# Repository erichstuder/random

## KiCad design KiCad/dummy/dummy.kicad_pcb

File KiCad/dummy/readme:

pcb with traces of different width

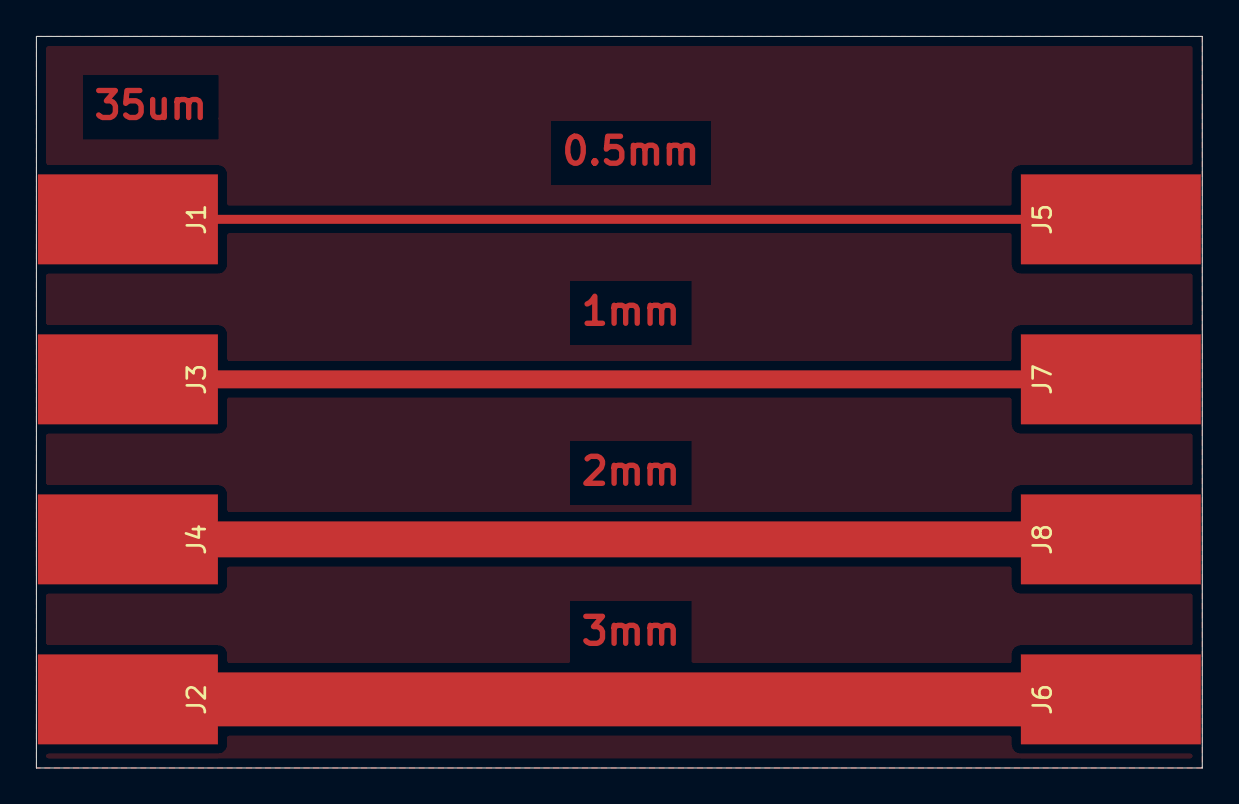
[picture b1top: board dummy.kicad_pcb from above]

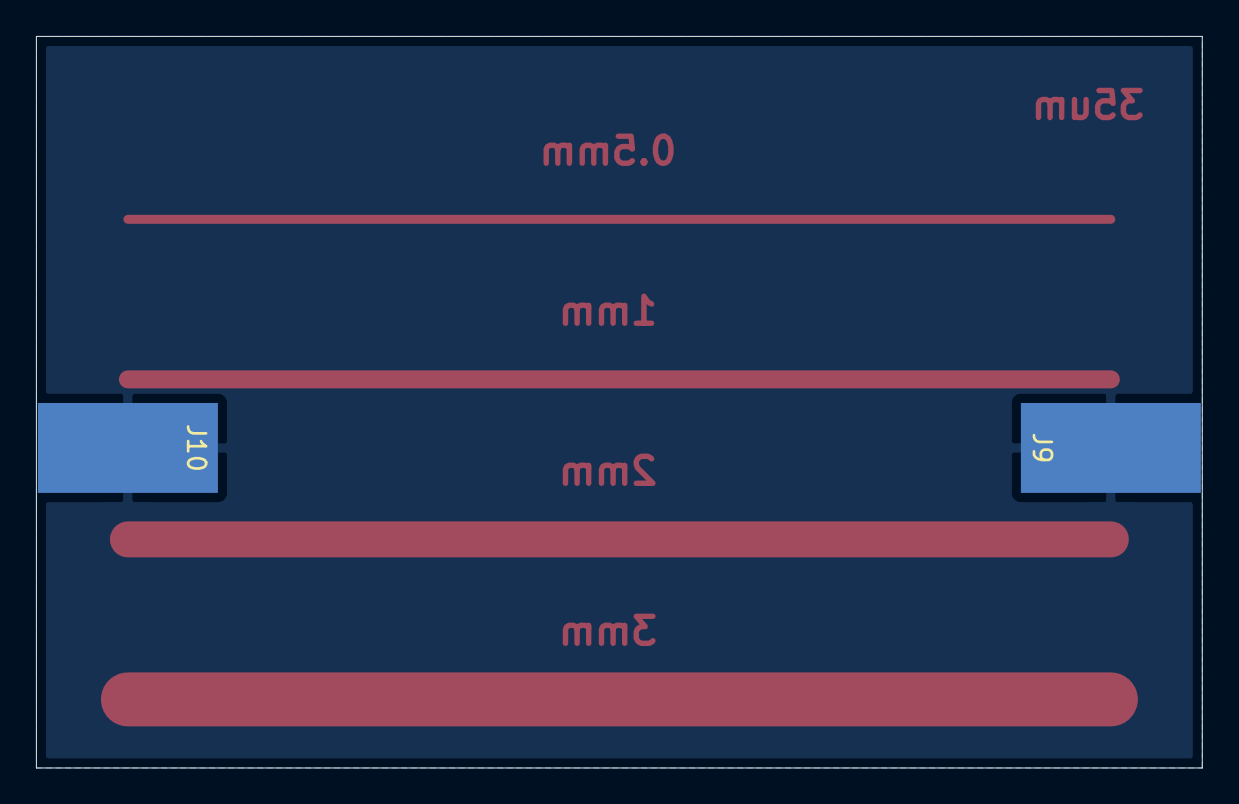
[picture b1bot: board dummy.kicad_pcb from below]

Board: 2 copper layers, 64.8 x 40.6 mm, 10 parts (2 on the bottom side), 5 nets.

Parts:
J1, J2, J3, J4, J5, J6, J7, J8, J9, J10: Conn_01x01_Female; SolderWirePad_1x01_SMD_5x10mm

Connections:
unnamed: J1.1, J5.1
unnamed: J2.1, J6.1
unnamed: J3.1, J7.1
unnamed: J4.1, J8.1
unnamed: J9.1, J10.1

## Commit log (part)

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2019-08-17 added new folder
2019-08-18 made it work for windows and some cleanup
2019-08-18 images for training created
2019-08-20 deleted old file
2019-08-29 added some rules for HDL languages
2019-09-03 example with parameters
2019-09-04 idea for an uart. But not yet compiling
2019-09-05 finally compiling
2019-09-05 resolved some more warnings
2019-09-07 initial commit of clock definition
2019-09-07 random commit
    test benches added
2019-09-07 simplified and tested UartTx
2019-09-07 added some stuff to ignore
2019-09-08 some try around with debugging possibilities
2019-09-09 added file to project
2019-09-10 top level design of I2C Master started
2019-09-11 some hacking with tasks (not compiling)
2019-09-11 random commit
2019-09-22 looks fine till now
    next step is to read from slave
2019-09-22 started cleaner setup of code
2019-09-25 made more files to increase readability
2019-09-26 some new files and more tryout
2019-09-28 ignoring *.bak files
2019-09-28 proof of conecept: abstraction with packages
2019-09-28 refactored to package usage
2019-09-28 added and integrated ReadBit as a package
2019-09-28 further work
2019-09-28 integrated readByte
2019-09-28 integrated SendStop
2019-09-29 some file reordering
2019-09-29 added some simple testing idea (not yet perfect)
2019-09-29 added another chapter
2019-09-30 started with error handling chapter
2019-10-01 finished chapter
2019-10-01 started next chapter
2019-10-02 added chapter about unit tests
2019-10-03 added Classes chapter
2019-10-05 test project for TCS34725 with arduino leonardo
2019-10-12 added Systems chapter
2019-10-12 added chapter about Concurrency
2019-10-14 added G15
2019-10-14 added some more lines
2019-10-26 inital commit
2019-10-27 first version of iot luxmeter
2019-10-27 a playaround project for Google Test
2020-04-05 creation of simple terminal for leonardo
2020-04-05 added unit tests
2020-04-10 bugfixes and minor modifications
2020-04-10 simple script for water detection
2020-04-25 added more leds for better visibility
2020-04-25 updated unit tests
2020-05-23 some code snippets
2020-05-23 another snippet
2020-06-14 didn't work
2020-06-20 initial creation
2020-06-27 rework and cleanup
2020-06-27 refactored for more clarity
2020-07-12 update modified submodule
2020-07-15 added locks
2020-07-18 ready to print
2020-07-18 sliced and files moved to folder
2020-07-18 some cleanup
2020-07-18 modified due to printing problems
2020-07-18 tryout of other print parameters
2020-07-19 simplified the model
2020-07-19 Moved from its own repository to here.
2020-07-20 added a grid and some cleanup
2020-07-25 did not workout as i expected but ok
2020-07-26 two pieces and bottom-up
2020-07-28 added some more findings
2020-08-01 modified for more stability and better fit
2020-08-02 first image
2020-08-15 minor changes
2020-08-22 slight modification
2020-08-29 renamed to base and further work
2020-08-29 minor modification for rendering stl file
2020-08-29 optimized slicing
2020-08-29 widened the hole for the screw nut for a less tight fit
2020-08-29 some contained parts are no longer recent
2020-08-29 improvements
    - thicker pcbs
    - prevent rotation by slider
2020-08-29 made 6 edge hole wider for easier insert of screw nut
2020-09-12 modification compiled and sliced
2020-09-20 modified and sliced
2020-09-20 sliced with Prusa PETG
2020-09-20 made bigger to have more detail
2020-09-20 mirrored the image
2020-09-20 sliced with 100% fill
2020-10-05 refined the model
2020-10-17 some tryouts to diffuse light
2020-10-17 modified and improved for first version
2020-10-17 increased height to improve handling
2020-10-17 some review findings
2020-10-17 noted down some findings
2020-10-24 deleted as it has bad orientation
2020-10-31 added slits for easier fit
2020-11-07 slit made more narrow to prevent damage
    - must be tested if slit not closed during print
2020-11-15 holder for leds
2020-11-15 a cup for the monitor
2020-11-21 latest stl
2020-11-21 initial commity
2020-12-05 improved buckle
2020-12-14 V2
    - added a rounding to base plate
    - marked as V2
2020-12-15 removed error under linux and corrected file path
2020-12-15 fixed error on linux and corrected file path
2020-12-15 made sample time dynamic and changed ADC channel
2020-12-15 ignoring session files
2020-12-15 script to run
2020-12-15 new branch and some changes
2020-12-15 modified for simpler device discovery and sampleTime is set
2020-12-21 first commit for useless box
2020-12-22 created a version without raspberry pi
2020-12-24 filtering the adc values
2020-12-25 more parts calculated
2020-12-25 new version for a hp screen
2020-12-28 added more parts of the arm
2020-12-29 reorganized project structure
2021-01-01 to be printed with flexible filament
2021-01-02 further work done
2021-01-10 modified for different switch
2021-01-10 version for another screen
2021-01-10 minor modifications for testing
2021-01-10 modified for new switch
2021-01-10 creation of electronics schematic
2021-01-24 further work for testing
2021-02-28 latest rendering
2021-02-28 minor modifications
2021-03-07 modified for usage in the box
2021-03-13 changed the angle
2021-03-13 minor change in wall thickness
2021-03-13 file no longer needed
2021-04-17 initial commit of battery cycler firmware
2021-04-17 added missing include
2021-04-17 infrastructure to measure cell current
2021-04-17 infrastructure for current controller tuning
2021-04-18 switched to python for the analysis
2021-04-28 moved to its own repository
2021-05-19 ignoring some file
2021-06-27 holder for bottles in a drawer
2021-06-27 for smaller bottles
2021-07-10 angular resolution 360 degree
2021-07-25 bugfix
2021-07-25 latest file
2021-08-25 remove some holes to keep stuff inside
2021-08-25 initial commit of production files
2021-08-27 correct position of hole
2021-08-27 bugfixes
2021-09-03 rename folder
2021-09-24 better usability
2021-09-24 prusa slicer file
2021-12-24 refactore, simplify and make more robust
2021-12-24 increase distance of separated parts to prevent intersection
2021-12-24 make cones slightly bigger to garanty overlap and prevent errors
2021-12-24 production files
2021-12-25 add brim for better adhesive
2021-12-25 cut off small plane to make sure first layer is extruded
2021-12-25 increase wall thickness for better printability
2021-12-25 reduce hole size for better printability
2021-12-25 new files based on changed scad-file
2021-12-27 add support material
2021-12-30 add some todos
2022-01-22 move pit
2022-01-22 optimize for printability
2022-01-23 split into upper and lower part
2022-01-25 set slice height to 0.05mm
2022-02-06 improve design and fix bugs
2022-02-12 360 degrees and modify plot settings
2022-02-15 some modifications
2022-02-18 two peaces
2022-02-20 printable
2022-03-05 use cpputest with docker
2022-03-05 lcd driver
2022-03-05 integrate temperature sensore
2022-03-05 unit tests for main.cpp
2022-03-26 initial commiat
2022-03-27 total rework
2022-03-27 parameter tuning
2022-04-03 refactoring
2022-04-03 sliced with windows and 3.4.1 slicer
2022-04-07 some optimizations
2022-04-07 smoother path
2022-04-09 change to cylinderical connector
2022-04-15 2 times twisted moebius strip
2022-04-18 intial commit
2022-04-18 creation of printing files
2022-04-29 add servo
2022-04-29 integrate display with servo
2022-05-02 add information about the hardware
2022-05-02 add more low power code
2022-05-03 add low power example
2022-05-03 add more findings
2022-05-03 add more measurements
2022-05-05 implement and integrate lowPower_1
2022-05-05 add wake-up and some led blinking
2022-05-05 minor corrections
2022-05-07 integration of display
2022-05-07 add homing
2022-05-07 update documentation
2022-05-07 update work
2022-06-07 add readme
2022-06-15 modify for cylindrical connector
2022-06-16 add hollow bar and tune dimensions - add hollow bar - tune dimensions of outter connector - tune wall thickness - add parameters file
2022-06-26 add horizontal joint
2022-06-26 make infill 100%
2022-07-02 multiple optimizations - thread was too tight - connector made a bit smaller for better fit - refactored the code for readability - minor changes for better printability
2022-07-17 add funnel
2022-08-14 remove unnecessary filed
2022-09-08 sliced
2022-09-09 improve printability
2022-09-10 slice
2022-09-10 improve handle
2022-09-10 bugfix and remove now old files
2022-10-23 created
2022-12-10 move moebius lamps to separate folder
2022-12-10 much faster rendering
2022-12-12 prepare for path integration
2022-12-14 add faces
2022-12-17 correct faces orientation
2023-03-25 knife handle
2023-04-12 round edges
2023-05-18 no longer needed
2023-05-28 mouseWheel_2.scad
2023-08-20 change the way the bar becomes long enough
2023-08-20 more work
2023-09-05 add some explanation
2023-09-05 move coding guidelines to a more general place
2023-09-24 more work on the process
2024-03-02 toothbrush holder
2024-04-21 optimize and delete unused file
2024-07-06 delete, no longer needed
2024-07-06 two different crc calculations, same result
2024-07-07 setup debugger
2024-08-18 remove no longer needed stuff
2024-08-18 add mandrel holder
2025-08-24 add some 3d parts
